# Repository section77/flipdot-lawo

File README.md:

# flipdot-lawo

Code repository for controlling the large Lawo flipdot display of Section 77.

## Contents

Currently this repository contains the following Arduino sketches:

* testpatterns: the four test patterns (all yellow, all black, alternating yellow/black, alternating black/yellow) of the OEM controller board
* random: flips random dots in random direction
* demo-window: displays a custom section77 logo with some random actions
* countdown: displays a countdown to UNIX timestamp 1,700,000,000 

## Hardware

The sketches are written for the Wemos LOLIN32 (v1.0.0) ESP32 board and require the corresponding board to be installed in the Arduino IDE. Since the ESP32 logic levels are at 3.3V, level converters (e.g. 74HCT245) are needed.

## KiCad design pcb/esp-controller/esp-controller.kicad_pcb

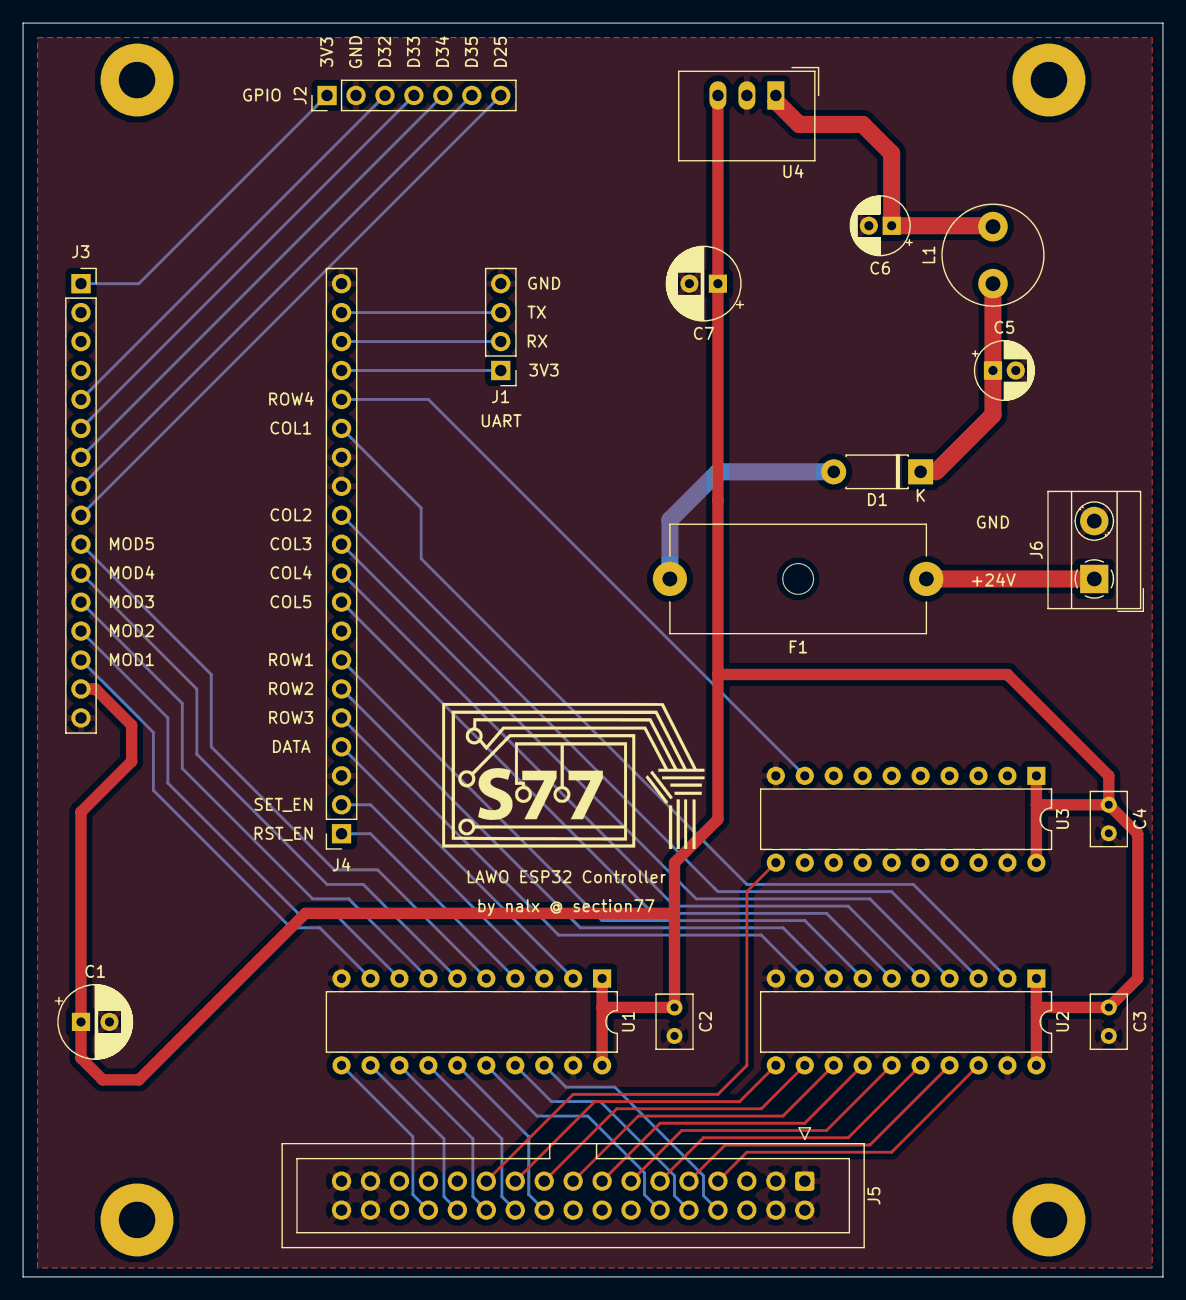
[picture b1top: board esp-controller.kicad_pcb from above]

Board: 2 copper layers, 100.0 x 110.0 mm, 21 parts (0 on the bottom side), 49 nets.

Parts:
C1, C7: 220 µF; CP_Radial_D6.3mm_P2.50mm
C2, C3, C4: 100 nF; C_Rect_L4.6mm_W3.0mm_P2.50mm_MKS02_FKP02
C5, C6: 4.7µF/50V; CP_Radial_D5.0mm_P2.00mm
D1: D_Schottky; D_DO-41_SOD81_P7.62mm_Horizontal
F1: Fuse; Fuseholder_Cylinder-5x20mm_Schurter_0031_8201_Horizontal_Op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
J1: UART; PinHeader_1x04_P2.54mm_Vertical
J2: GPIO; PinHeader_1x07_P2.54mm_Vertical
J3: ESP_LEFT; PinSocket_1x16_P2.54mm_Vertical
J4: ESP_RIGHT; PinSocket_1x20_P2.54mm_Vertical
J5: Conn_02x17_Odd_Even; IDC-Header_2x17_P2.54mm_Vertical
J6: Screw_Terminal_01x02; TerminalBlock_MetzConnect_Type101_RT01602HBWC_1x02_P5.08mm_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
L1: 8.2 µH/1.5 A/0.08 O; L_Radial_D8.7mm_P5.00mm_Fastron_07HCP
Ref**: Val**; section77_logo_kicad
U1, U2, U3: 74HCT245; DIP-20_W7.62mm
U4: TSR_1-2450; Converter_DCDC_TRACO_TSR-1_THT

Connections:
+5V: C1.1, C2.1, C3.1, C4.1, C7.1, J3.15, U1.1, U1.20, U2.1, U2.20, U3.1, U3.20, U4.3
+24V: D1.2, F1.2
GND: C1.2, C2.2, C3.2, C4.2, C5.2, C6.2, C7.2, J1.4, J2.2, J3.16, J4.3, J4.13, J4.14, J4.20, J5.1, J5.2, J5.3, J5.4, J5.31, J5.32, J5.33, J5.34, J6.2, U1.10, U1.19, U2.10, U2.19, U3.10, U3.19, U4.2
unnamed: C5.1, D1.1, L1.1
unnamed: C6.1, L1.2, U4.1
unnamed: F1.1, J6.1
unnamed: J1.1, J4.17
unnamed: J1.2, J4.18
unnamed: J1.3, J4.19
unnamed: J2.1, J3.1
unnamed: J2.3, J3.5
unnamed: J2.4, J3.6
unnamed: J2.5, J3.7
unnamed: J2.6, J3.8
unnamed: J2.7, J3.9
unnamed: J3.10, U1.5
unnamed: J3.11, U1.6
unnamed: J3.12, U1.7
unnamed: J3.13, U1.8
unnamed: J3.14, U1.9
unnamed: J4.1, U1.4
unnamed: J4.2, U1.3
unnamed: J4.4, U1.2
unnamed: J4.5, U2.9
unnamed: J4.6, U2.8
unnamed: J4.7, U2.7
unnamed: J4.9, U2.6
unnamed: J4.10, U2.5
unnamed: J4.11, U2.4
unnamed: J4.12, U2.3
unnamed: J4.15, U2.2
unnamed: J4.16, U3.9
unnamed: J5.7, U2.18
unnamed: J5.8, U1.18
unnamed: J5.9, U2.17
unnamed: J5.10, U1.17
unnamed: J5.11, U2.16
unnamed: J5.12, U1.16
unnamed: J5.13, U2.15
unnamed: J5.15, U2.14
unnamed: J5.17, U2.13
unnamed: J5.19, U2.12
unnamed: J5.20, U1.15
unnamed: J5.21, U2.11
unnamed: J5.22, U1.14
unnamed: J5.23, U3.11
unnamed: J5.24, U1.13
unnamed: J5.26, U1.12
unnamed: J5.28, U1.11

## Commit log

2018-08-25 new sketch that implements OEM test patterns
2018-09-04 testpattern and addressing bugfixes
2018-09-18 final pin assignments for lolin32
2018-09-18 add sketch flipping random dots
2020-08-08 add logo sketch with random actions
2020-08-12 fix loop counter type and reduce time between actions
2022-03-01 add PCB files
2022-03-01 add adjusted sketch for modified display above door
    half-width module has been removed and custom PCB is used
2023-11-03 Code for countdown to Unix-Birthday 1700000000 added
2023-11-03 Flipdot-Display Emulator added
2023-11-05 Update README.md
    added countdown
2023-11-28 Added countdown to christmas
2023-12-12 Bugfix: Flip all dots to blank once per hour to blank stale dots
